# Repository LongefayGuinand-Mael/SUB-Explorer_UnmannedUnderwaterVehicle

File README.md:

<br>
	<p align="center">
		<h1 align="center"> :warning:   WARNING   :warning: </h1>
	</p>
<br>

This project was made in French only for an Academic Work. So please consider that whole project files names, reports and other are only in French. This project was made during our last year in the ESME Sudria Engineering School between October 2022 and March 2023. 

Please note that this README.md is only a preface to all the work done during these 6 months of the project, if you wish to know more after reading this README, please refer to our report `/Rapports/Rapport Projet Drone Sous-Marin.pdf` (written in French).

------------------------------------------------------
------------------------------------------------------

<br>
	<p align="center">
	    <h1 align="center">Unmanned Underwater Vehicle - Sub-Explorer</h1>
	</p>
</br>

Dans le cadre de notre dernière année academic d'ingénierie à l'ESME Sudria (Master 2), mon groupe et moi-même avons travaillé pendant une durée de 6 mois sur un drone sous-marin ayant pour objectif principal la recherche scientifique. Dans le cadre de notre projet, nous avons mis en place diverses choses afin de mener à bien cet objectif et nous sommes arrivé à un résultat très concluant. Veuillez à noter que le README.md n'est qu'une préface à tout le travail effectué lors de ces 6 mois de projet, si vous avez pour souhait de d'en savoir plus après lecture de ce README, veuillez à vous référer à notre rapport `/Rapports/Rapport Projet Drone Sous-Marin.pdf`.

Ce projet c'est principalement articulé avec les parties suivantes :
- Définition du Cahier des charges 
- Veille technologique :
	- Recherche des Composants
	- Mise en place d'un schéma électrique
	- Réalisation des Printed Circuit Board
- Programmation (Python)
- Modélisation structurelle 3D du drone   
*Les autres parties (moins techniques) sont trouvables dans le rapport complet de notre projet de fin d'études.*

------------------------------------------------------

### Sommaire :
1. [Définition du Cahier des Charges](#cahier-des-charges)
2. [Choix des Composants](#choix-composants)
3. [Schémas Électroniques](#schémas-électroniques)
4. [Réalisation des Printed Circuit Board (PCB)](#pcb)
5. [Programmation](#programmation)
6. [Modélisation structurelle du drone](#modélisation-3d)
7. [Noms et Contacts des étudiants ayant travaillé sur le projet](#contacts)

------------------------------------------------------

<br>
	<p align="center">
	    <h2 align="center">Définition du Cahier des Charges</h2>
	</p>
</br>

### Introduction :
Notre objectif est de concevoir un drone sous-marin dans son intégralité, allant de la définition du cahier des charges à sa conception électronique et  3D. Pour mettre à bien notre projet, l'objectif premier est de mettre au point un système de pilotage efficace pour notre drone sous-marin, en veillant à sa motorisation directionnelle, à sa radiocommunication et à son design 3D. Nous prévoyons également d'intégrer des outils scientifiques à notre plateforme, ainsi que de travailler sur une optimisation de son design. En somme, ce projet est l'opportunité pour nous de mettre en pratique nos connaissances en matière de systèmes embarqués, tout en nous confrontant à des défis technologiques passionnants.
Dans le cadre de ce projet, nous mettons d’abord la priorité sur le pilotage de la plateforme (motorisation directionnelle, radiocommunication). Les outils scientifiques et l’optimisation du design seront vus dans un second temps.

### Fonctionnalités :
1. _Les fonctionnalités primaires :_
	- UUV manœuvrable sur 3 dimensions. → Motorisation directionnelle (lacet, tangage, profondeur, direction).
	- L’UUV est radiocommandé. → Conception d’un flotteur permettant de maintenir l’antenne (récepteur 2.4GHz) hors de l’eau afin de simplifier la communication entre le système de pilotage et la machine.
→ Utilisation d’une télécommande et d’un récepteur 2.4GHz.
	- Le drone doit être étanche afin de protéger le système de l’eau.
	- Le drone doit également répondre à une limite de taille afin qu'il puisse se déplacer dans des espaces restreints. Nous avons donc pour objectif de taille que le drone fasse maximum 600 mm de longueur et 300 mm de diamètre.
	- La flottaison de l’UUV doit être neutre : nous devons faire en sorte d’obtenir un équilibre entre le poids et la poussée d’Archimède du drone.
	- Nous voulons que le drone puisse effectuer des missions scientifiques d’une durée minimum de 30 minutes - 1 heure. Cela nous défini une contrainte d'autonomie.
2. _Les fonctionnalités secondaires :_
	- Retour vidéo (mise en place d’une caméra embarquée pour pouvoir voir ce qui se trouve dans l’environnement du drone même lorsque celui-ci n'est pas visible depuis la surface).
	- Système d’éclairage LED afin de pouvoir voir convenablement l’environnement où se trouve le drone via le retour caméra.
	- Capteurs de température et de pression (utile pour de la recherche et pour assurer le maintien structurel du drône en fonction de la pression exercée sur lui de part la pression de l’eau - liée à la profondeur à laquelle il se trouve).
	- Structure résistante aux chocs et protégeant les composants fragiles pouvant être exposés à l’extérieur du drone (par exemple les capteurs ou encore les hélices des moteurs).
3. _Les fonctionnalités intéressantes supplémentaires :_
	- Ajout de systèmes pour la collecte de données scientifiques : échantillonneur, sondeur, GPS, divers nouveau capteur, etc.
	- Intégrer une capacité de stockage et de récupération rapide des données.
	- Développement d’une application mobile pour le pilotage de tout le drone (contrôle de
son déplacement dans l’espace et des éléments scientifiques qu’il embarque et permettant l’affichage du flux vidéo en temps réel).

### Schéma Bloc Fonctionnel du Projet :

------------------------------------------------------

<br>
	<p align="center">
	    <h2 align="center">Choix des Composants</h2>
	</p>
</br>

*Toutes les datasheets des composants utilisés sont regroupées dans les fichiers du projet dans le dossier `/DatasheetsComposents`.*

### Intelligences Numériques :
Nous utilisons dans ce projet 2 Raspberry Pi.   
- La première est une **Rasberry Pi 4B (de 4 à 8 Go RAM)**. Cette Raspberry Pi nous permet la réception des données envoyées par la télécommande et donc par l'utilisateur afin de contrôler les moteurs et l'allumage ou non des LED qu'il embarque.   
- La seconde est une **Raspberry Pi 3B+**. Cette Raspberry Pi, quant-à elle, nous permet d'éberger un WebServeur local afin d'avoir un retour caméra et capteurs (afin de connaître, même si nous ne voyons plus le drone depuis la surface, de connaître l'environnement dans lequel il est).

### Caméra Embarquée :
Comme dit plus haut, nous avons besoin de savoir consatemment l'environnement du drone même lorsque celui-ci n'est pas visible depuis la surface. Ainsi, nous utilisons une caméra embarquée dans le drone. Par soucis de simplicité et surtout de qualité, nous avons choisi de prendre la **Camera Module V2 Raspberry** (existe maintenant également avec un autofocus). Cette caméra embarqué nous permet d'avoir une excélente qualité (1280x720 pixel) avec un haut débit (jusqu'à 24 fps) et puis elle est nativement supportée par la Rasberry Pi 3B+ qui va l'utiliser et envoyer son stream vidéo sur le WebServeur qu'elle host.

### Récepteur Radio + Télécommande :
Dans notre projet, nous avons eu la volonté de contrôler notre drone à distance en imaginant un moyen d'éviter d'avoir un drone qui embarque un enrouleur de câble pour pouvoir communiquer avec l'utilisateur via ce qui s'apparente à un câble d'Arianne. Ainsi, nous avons choisi de mettre en place ce câble d'Arianne entre notre sous-marin et un flotteur. Ce flotteur pourra ainsi embarquer 2 antennes. L'une étant l'antenne radio (2.4GHz) et l'autre une antenne WiFi (dont nous reparlerons plus tard).

Nous avons donc prit un récepteur radio **FS-IA6B**. Ce récepteur 2.4GHz (fréquence laissée libre pour la science et d'autres recherche) va nous servirà communiquer avec notre sous-marin. En plus de ce récepteur, nous avons une télécommande FlySky (utilisée dans le modélisme et qui convient très bien à notre projet pour le moment). 

### Composants ayant un lien avec le déplacement du drone :
La phase la plus technique dans ce projet est le déplacement du sous-marin car en plus de la réception des données de la télécommande redio, il faut adapter les données récupérées en données fiables pour contrôler convenablement nos moteurs. 

Nous avons 2 types de moteurs : 
- 4 moteurs pas-à-pas **17HS08-1004S** commandé à l'aide d'un driver moteur **A4988-1182** par la Raspberry Pi 4B.
- 1 moteur à courant continu de la marque **lichifit** (utilisé dans le modélisme naval) commandé à l'aide d'un driver moteur **DRV8838** également par la Raspberry Pi 4B.

Les moteurs pas-à-pas seront utilisés pour des mouvements plus précis tels que les mouvements translatifs lattéraux et de profondeur et pour les mouvement rotatifs (lacet et tangage).    
Le moteur à courant continu sera quant-à lui utilisé uniquement pour la translation avant-arrière et sera notre propulseur principal.

### Composants ayant un lien avec la récupération de données (capteurs) :
Dans notre sous-marin, nous souhaiton à minima pouvoir récupérer deux données, la température et la pression. 

Pour le capteur de température, nous avons choisi le capteur **DS18B20**. Le choix de ce composant à été assez intuitif puisque celui-ci ressemble à une sonde, il est étanche et à une plage d'utilisation large avec une précision de 0.0625°C.

Pour le capteur de pression, nous avons choisi le capteur **MS5837-30BA**. Ce capteur fonctionne en I²C, il est étanche et a une plage de fonctionnement allant jusqu'à 30 bar (jusqu'à 290m de profondeur dans l'eau) avec une précision de 0.2mBar (soit ±2mm).

À l'avenir, nous imaginons pouvoir rajouter des capteurs tels que celui de salénité de l'eau et de pollution maritime ou encore un capteur de tangage pour la stabilisation du drone.

### Composants autres :
Les autres composants sont divers. 

Nous avons ici un convertisseur Buck-Boost **DFR0753** afin de pouvoir allimenter d'une tension de 5V les 2 Raspberry Pi mais d'une tension de 9V les différents moteurs et le bandeau LED.

En parlant du **bandeau LED**, nous avons imaginé embarquer des LED dans le sous-marin afin de permettre de les activer ou non pour pouvoir, en toutes circonstances et sur demande de l'utilisateur, de voir l'environnement de travail du drone sous-marin qu'il soit visible depuis la surface ou pas. Le bandeau LED est unicolore blanc, certifié IP67 (étanche poussière et eau), et peut être allimenté jusqu'à 12V. Nous l'utilisons avec une tension d'allimentation de 9V largement suffisante pour nous.

------------------------------------------------------

<br>
	<p align="center">
	    <h2 align="center">Schémas Électroniques</h2>
	</p>
</br>

*Pour une meilleure qualité, les images des schémas électroniques sont trouvables dans les fichiers du projet dans le dossier `/SchémasÉlectroniques+PCB`) Leurs noms étants : `Schéma Électronique - Raspberry Pi 3B+.png` et `Schéma Électronique - Raspberry Pi 4B.png`.*

Après l'analyse de tous les composants, nous avons mis en place 2 schémas électroniques. L'un concerne la Raspberry Pi 3B+ et l'autre la Raspberry Pi 4B.

### Partie Raspberry Pi 3B+ :

Pour cette partie, nous retrouvons dans le schéma électronique les capteurs de température et de pression. Il est à noté également que nous avons de géré par cette Raspberry Pi la caméra embarquée.

### Partie Raspberry Pi 4B :

Pour cette partie, nous retrouvons dans le schéma électronique les 4 moteurs pas-à-pas ainsi que leurs drivers respectifs, le moteur à courant continu et son driver, le bandeau LED, le récepteur 2.4GHz et des pins de branchement pour le convertisseur Buck-Boost (9V à 5V). 

***À Noter :*** *Les fichiers Fusion360 ayants permis de faire les schémas électroniques ainsi que les PCB sont trouvables dans les fichiers du projet dans le dossier `/SchémasÉlectroniques+PCB/FichiersFusion`.*

------------------------------------------------------

<br>
	<p align="center">
	    <h2 align="center">Réalisation des Printed Circuit Board (PCB)</h2>
	</p>
</br>

*Fichiers de conception des PCB sont trouvables dans les fichiers du projet dans le dossier `/SchémasÉlectroniques+PCB/FichiersConceptionPCB`. Un dossier regroupe les fichiers utiles par un fabriquant de PCB pour faire celui de la Raspberry Pi 3B+ et un autre dossier est pour celui de la Raspberry Pi 4B.*

Cette partie ne pourra pas être beaucoup développée à l'écrit. Pour faire au plus simple, suite à la mise en place de nos 2 schémas électroniques, nous avons pu mettre en place 2 PCB qui seront utilisés pour notre projet (un pour chacune des intelligences électroniques). Sur le PCB de la Raspberry Pi 3B+ on peut y retrouver les branchements des différents capteurs tandis que sur le PCB de la Raspberry Pi 4B on y retrouve tous les composants utiles pour la réceptions des commandes de l'utilisateurs et les différents systèmes et branchements pour les moteurs et bandeau LED (en outre, tout ce qui est contrôllable par l'utilisateur à distance). 

La seconde chose importante mise en place est la définition de contraintes de dimentionnement afin de permettre aux 2 PCB de se brancher directement sur les Raspberry Pi. Ces contraintes sont principalement liée aux composants internes des Raspberry Pi et leurs hauteurs qui peuvent être génantes (dans les grandes lignes, ça regroupe les composants tels que celle du port éthernet, des ports USB, port de branchement caméra, port Jack et HDMI).

***Rappel :*** *Les fichiers Fusion360 ayants permis de faire les schémas électroniques ainsi que les PCB sont trouvables dans les fichiers du projet dans le dossier `/SchémasÉlectroniques+PCB/FichiersFusion`.*

------------------------------------------------------

<br>
	<p align="center">
	    <h2 align="center">Programmation (Python)</h2>
	</p>
</br>

*Tous les fichiers de programmation sont regroupées dans les fichiers du projet dans le dossier `/Programmation/Code`. Dans ce dossier on peut y retrouver les codes en Python (`.py`) ainsi que des logigrammes des programmes (au format `.png`).* 

Pour commencer, nous avons 2 intelligences numériques (1 Raspberry Pi 3B+ & 1 Raspberry Pi 4B) qui vont fonctionner simultannément mais de manière totalement distincte l'une de l'autre. Ainsi, nous exposons ci-dessous les logigrammes des programmes des 2 intelligences numériques : 

### Partie Raspberry Pi 3B+ :

Nous pouvons retrouver 2 étapes, l'initialisation et le fonctionnement. L'initialisation nous permet d'instancier les divers pins de la Raspberry que nous utilisons par la suite dans notre code ainsi que les multiples librairies utilisées. La phase de fonctionnement permet l'hébergement et l'envoie du stream de la caméra embarquée sur le WebServeur local de la Raspberry Pi 3B+. Il sera possible par la suite de créer un multi-thread afin de pouvoir récupérer en parallèle du WebServeur des données de capteurs pour les ajouter au retour caméra sur la page Web hébergée (*un début de code dans ce sens est retrouvable sous le nom `TempPrint_CameraWebLocal.py`*).

### Partie Raspberry Pi 4B :

Tout comme pour la Raspberry Pi 3B+, nous pouvons y voir qu'il y a 2 étapes dans ce logigramme, l'initialisation et le fonctionnement en temps-réel avec la mise en place d'un multi-thread ce qui équivaut à l'utilisation de plusieurs coeurs du processeur de la Raspberry Pi 4B qui se charge de ce code. *On peut également retrouver le programme de récupération des données réceptionnées depuis la télécommande radio sur le logigramme `Logigramme Pi4B (2) - SUB-Explorer.png` mit dans le fichier `/Programmation/LogigrammesExplicatifs/`.*

------------------------------------------------------

<br>
	<p align="center">
	    <h2 align="center">Modélisation Structurelle du Drone</h2>
	</p>
</br>

Voici une image de l'assemblage total des pièces imprimées en 3D de notre drone : 

*Pour une meilleure qualité, l’image de l'assemblage de la modélisation structurelle du drone sont trouvables dans les fichiers du projet (au niveau de la racine). Son nom étant : `Assemblage3D.png`.*   

Voici également une vidéo montrant l'**ordre assemblage des quelques 28 pièces (_vis non-incluses_)** composants notre sous-marin : 

https://user-images.githubusercontent.com/80823327/229296633-9bad1075-d35f-4a4c-87c2-66e0a59497dc.mp4
   
**Concernant les fichiers 3D de chacune des pièces ainsi que de l'assemblage, ces fichiers sont trouvables dans les fichiers du projet dans le dossier `/Modélisation3D`.**

------------------------------------------------------

<br>
	<p align="center">
	    <h2 align="center">Noms et Contacts</h2>
	</p>
</br>

-------------------------------------
-------------------------------------
## License
***© COPYRIGHT - All Rights Reserved - Zapata Industry (LONGEFAY-PIOT-POPESCO)***  
***Important :*** *Afin de poursuivre le projet, merci de nous contacter sur LinkedIn pour avoir notre approbation.*

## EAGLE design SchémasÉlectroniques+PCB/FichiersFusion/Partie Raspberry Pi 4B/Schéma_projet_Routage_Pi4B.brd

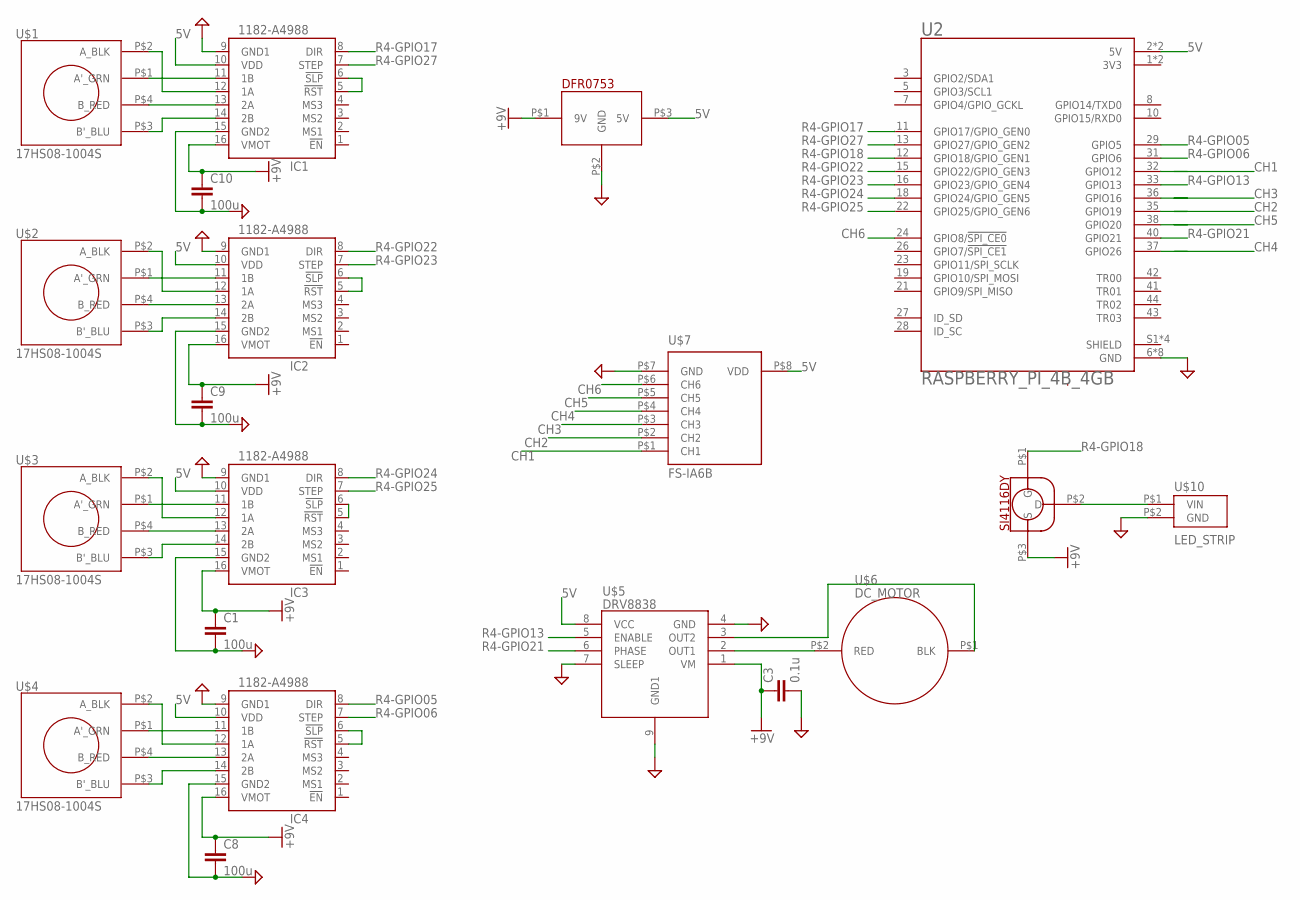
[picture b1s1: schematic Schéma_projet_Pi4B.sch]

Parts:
C1, C8, C9, C10: 100u; C0603
C3: 0.1u; C0603
IC1, IC2, IC3, IC4: 1182-A4988; A4988
U2: RASPBERRY_PI_4B_4GB; MODULE_RASPBERRY_PI_4B_4GB
U$1, U$2, U$3, U$4: 17HS08-1004S
U$5: DRV8838
U$6: DC_MOTOR
U$7: FS-IA6B
U$8: SI4116DY
U$10: LED_STRIP
U$11: DFR0753

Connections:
3V3: U2.1 (3V3), U2.17 (3V3)
5V: IC1.10 (VDD), IC2.10 (VDD), IC3.10 (VDD), IC4.10 (VDD), U2.2 (5V), U2.4 (5V), U$5.8 (VCC), U$7.P$8 (VDD), U$11.P$3 (5V)
+9V: C1.1, C8.1, C9.1, C10.1, IC1.16 (VMOT), IC2.16 (VMOT), IC3.16 (VMOT), IC4.16 (VMOT), U$8.P$3 (S), U$11.P$1 (9V)
AGND: C1.2, C3.2, IC2.9 (GND1), IC3.9 (GND1), IC3.15 (GND2), IC4.9 (GND1), U2.6 (GND), U2.9 (GND), U2.14 (GND), U2.20 (GND), U2.25 (GND), U2.30 (GND), U2.34 (GND), U2.39 (GND), U$5.4 (GND), U$5.7 (SLEEP), U$5.9 (GND1), U$7.P$7 (GND), U$10.P$2 (GND), U$11.P$2 (GND)
CH1: U$7.P$1 (CH1)
CH2: U$7.P$2 (CH2)
CH3: U$7.P$3 (CH3)
CH4: U$7.P$4 (CH4)
CH5: U$7.P$5 (CH5)
CH6: U2.24 (GPIO8/!SPI_CE0!), U$7.P$6 (CH6)
unnamed: C8.2, IC4.15 (GND2)
unnamed: U$5.3 (OUT2), U$6.P$1 (BLK)
unnamed: U$5.2 (OUT1), U$6.P$2 (RED)
unnamed: IC1.12 (1A), U$1.P$2 (A_BLK)
unnamed: IC1.11 (1B), U$1.P$1 (A'_GRN)
unnamed: IC1.13 (2A), U$1.P$4 (B_RED)
unnamed: IC1.14 (2B), U$1.P$3 (B'_BLU)
unnamed: IC2.12 (1A), U$2.P$2 (A_BLK)
unnamed: IC2.11 (1B), U$2.P$1 (A'_GRN)
unnamed: IC2.13 (2A), U$2.P$4 (B_RED)
unnamed: IC2.14 (2B), U$2.P$3 (B'_BLU)
unnamed: IC3.12 (1A), U$3.P$2 (A_BLK)
unnamed: IC3.11 (1B), U$3.P$1 (A'_GRN)
unnamed: IC3.13 (2A), U$3.P$4 (B_RED)
unnamed: IC3.14 (2B), U$3.P$3 (B'_BLU)
unnamed: IC4.12 (1A), U$4.P$2 (A_BLK)
unnamed: IC4.11 (1B), U$4.P$1 (A'_GRN)
unnamed: IC4.13 (2A), U$4.P$4 (B_RED)
unnamed: IC4.14 (2B), U$4.P$3 (B'_BLU)
unnamed: C3.1, U$5.1 (VM)
unnamed: U$8.P$2 (D), U$10.P$1 (VIN)
unnamed: IC4.5 (!RST), IC4.6 (!SLP)
unnamed: IC3.5 (!RST), IC3.6 (!SLP)
unnamed: IC2.5 (!RST), IC2.6 (!SLP)
unnamed: IC1.5 (!RST), IC1.6 (!SLP)
unnamed: C10.2, IC1.15 (GND2)
unnamed: C9.2, IC2.15 (GND2)
R4-GPIO05: IC4.8 (DIR), U2.29 (GPIO5)
R4-GPIO06: IC4.7 (STEP), U2.31 (GPIO6)
R4-GPIO13: U2.33 (GPIO13), U$5.5 (ENABLE)
R4-GPIO17: IC1.8 (DIR), U2.11 (GPIO17/GPIO_GEN0)
R4-GPIO18: U2.12 (GPIO18/GPIO_GEN1), U$8.P$1 (G)
R4-GPIO21: U2.40 (GPIO21), U$5.6 (PHASE)
R4-GPIO22: IC2.8 (DIR), U2.15 (GPIO22/GPIO_GEN3)
R4-GPIO23: IC2.7 (STEP), U2.16 (GPIO23/GPIO_GEN4)
R4-GPIO24: IC3.8 (DIR), U2.18 (GPIO24/GPIO_GEN5)
R4-GPIO25: IC3.7 (STEP), U2.22 (GPIO25/GPIO_GEN6)
R4-GPIO27: IC1.7 (STEP), U2.13 (GPIO27/GPIO_GEN2)
SHIELD: U2.S1 (SHIELD), U2.S2 (SHIELD), U2.S3 (SHIELD), U2.S4 (SHIELD)

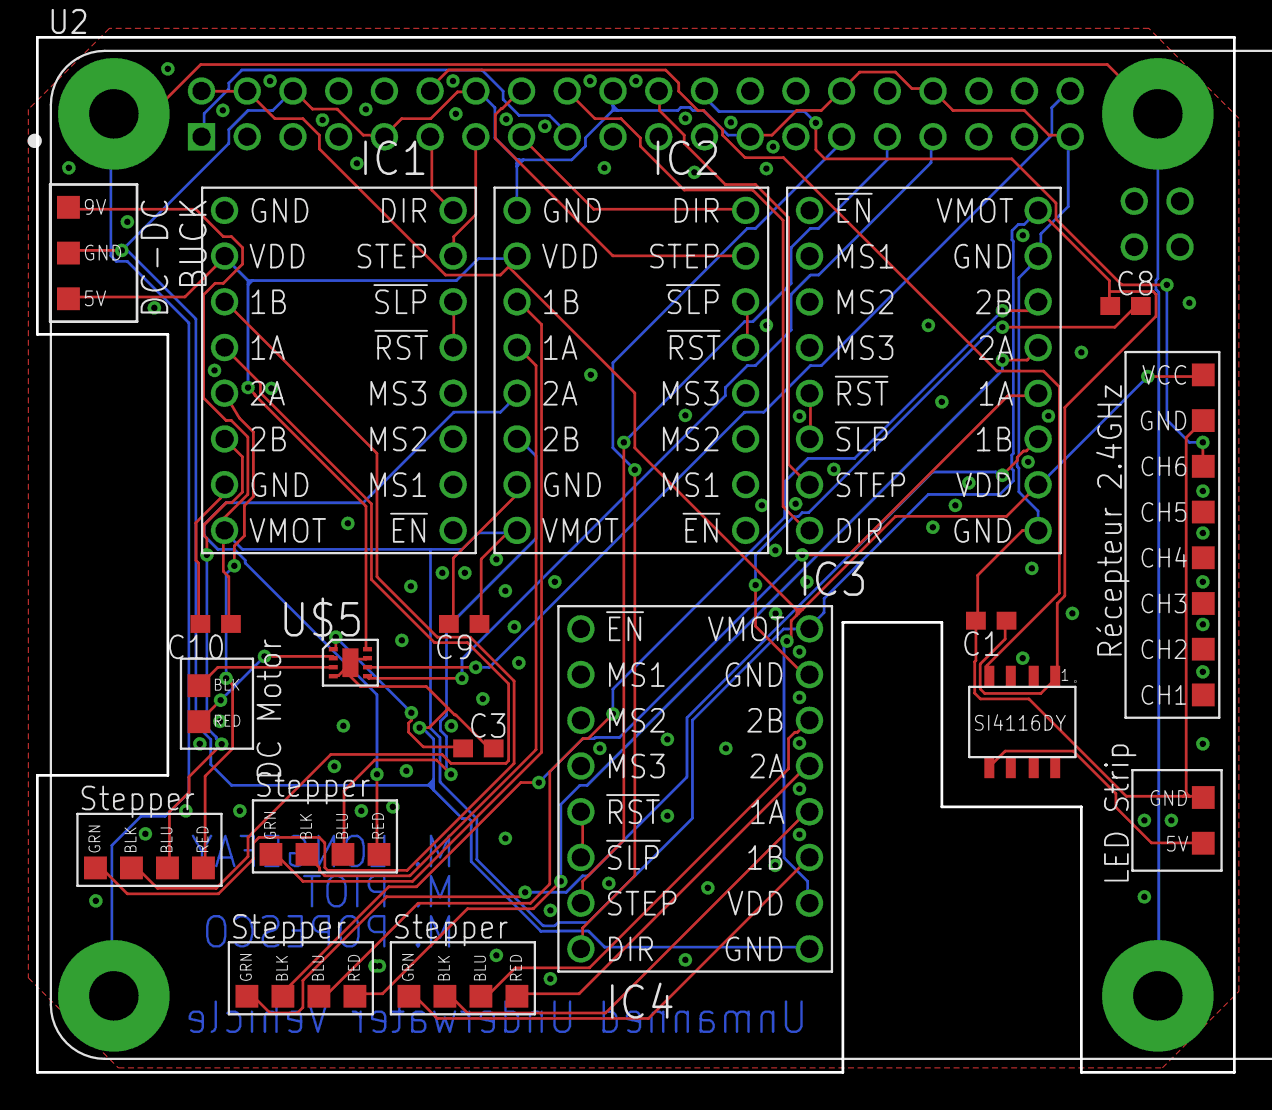
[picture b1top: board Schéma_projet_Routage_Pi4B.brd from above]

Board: 2 copper layers, 66.5 x 57.5 mm, 20 parts (0 on the bottom side), 44 nets.

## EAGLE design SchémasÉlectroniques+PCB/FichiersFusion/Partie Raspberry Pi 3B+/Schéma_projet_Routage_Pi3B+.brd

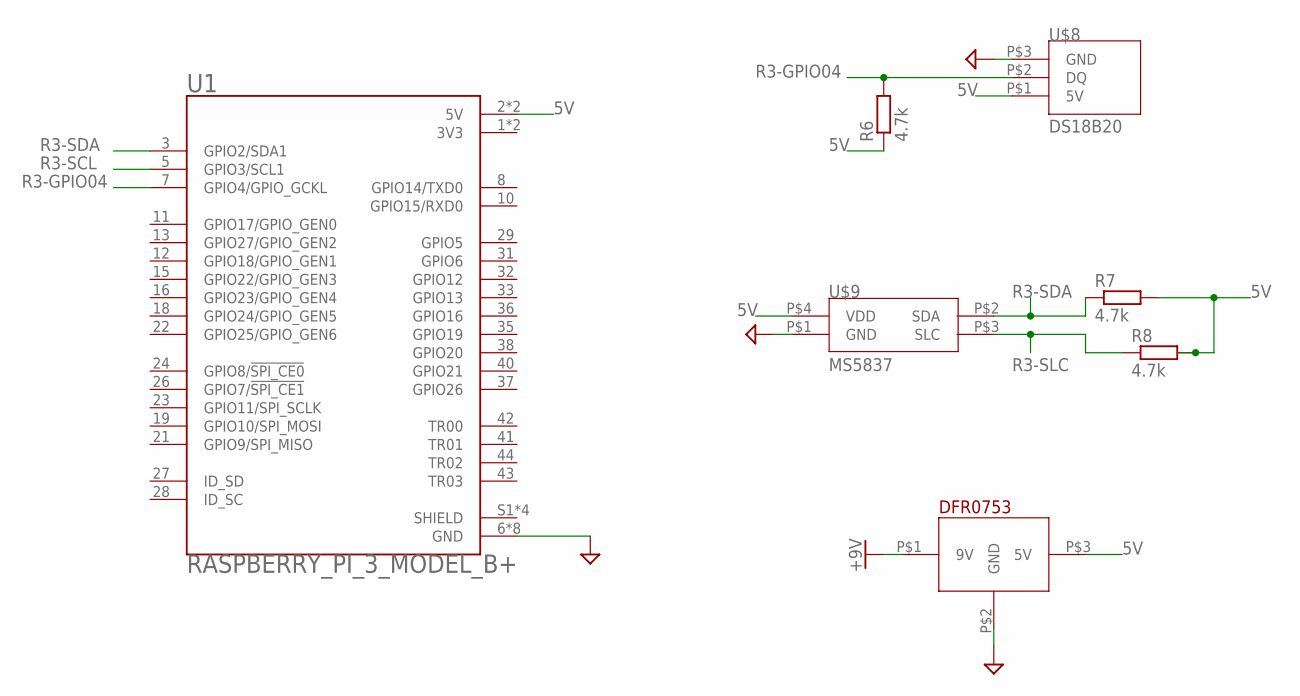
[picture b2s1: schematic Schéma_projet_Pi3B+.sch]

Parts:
R6, R7, R8: 4.7k; R0603
U1: RASPBERRY_PI_3_MODEL_B+; MODULE_RASPBERRY_PI_3_MODEL_B+
U$8: DS18B20
U$9: MS5837
U$11: DFR0753

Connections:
3V3: U1.1 (3V3), U1.17 (3V3)
5V: R6.1, R7.2, R8.2, U1.2 (5V), U1.4 (5V), U$8.P$1 (5V), U$9.P$4 (VDD), U$11.P$3 (5V)
+9V: U$11.P$1 (9V)
AGND: U1.6 (GND), U1.9 (GND), U1.14 (GND), U1.20 (GND), U1.25 (GND), U1.30 (GND), U1.34 (GND), U1.39 (GND), U$8.P$3 (GND), U$9.P$1 (GND), U$11.P$2 (GND)
R3-GPIO04: R6.2, U1.7 (GPIO4/GPIO_GCKL), U$8.P$2 (DQ)
R3-SCL: U1.5 (GPIO3/SCL1)
R3-SDA: R7.1, U1.3 (GPIO2/SDA1), U$9.P$2 (SDA)
R3-SLC: R8.1, U$9.P$3 (SLC)
SHIELD: U1.S1 (SHIELD), U1.S2 (SHIELD), U1.S3 (SHIELD), U1.S4 (SHIELD)

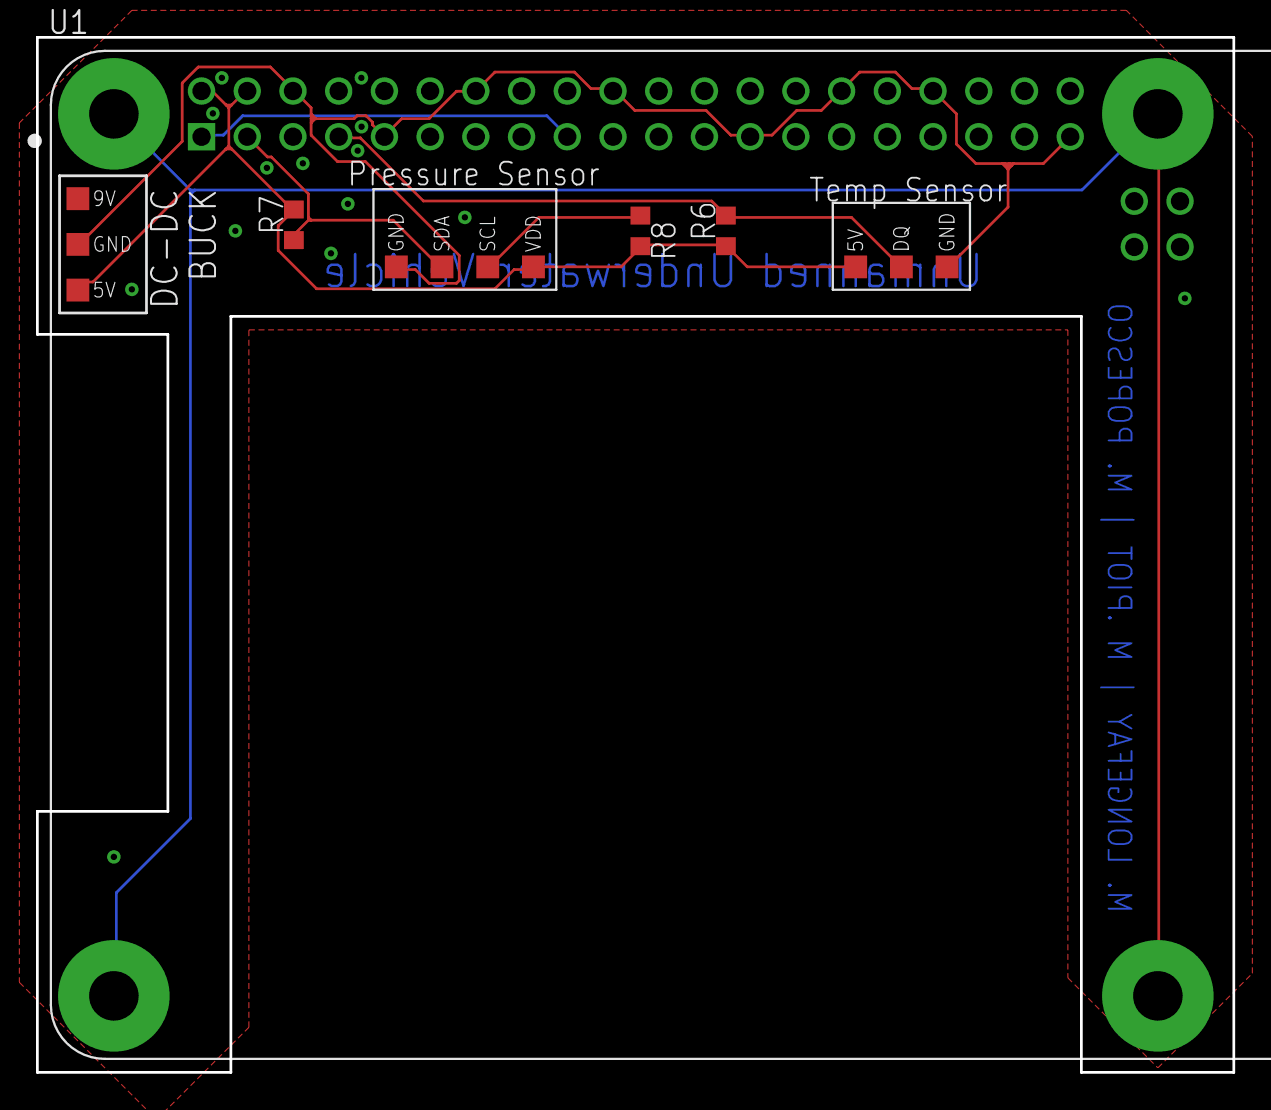
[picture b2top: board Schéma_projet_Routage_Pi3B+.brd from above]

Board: 2 copper layers, 66.5 x 57.5 mm, 7 parts (0 on the bottom side), 7 nets.

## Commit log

2023-04-01 Added all project files (1/2)
    All the files needed to redo or continue the project.
2023-04-01 Added all project files (2/2)
    All the files needed to redo or continue the project.

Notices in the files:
README.md:
License:
© COPYRIGHT - All Rights Reserved - Zapata Industry (LONGEFAY-PIOT-POPESCO)
Important :*** *Afin de poursuivre le projet, merci de nous contacter sur LinkedIn pour avoir notre approbation.
